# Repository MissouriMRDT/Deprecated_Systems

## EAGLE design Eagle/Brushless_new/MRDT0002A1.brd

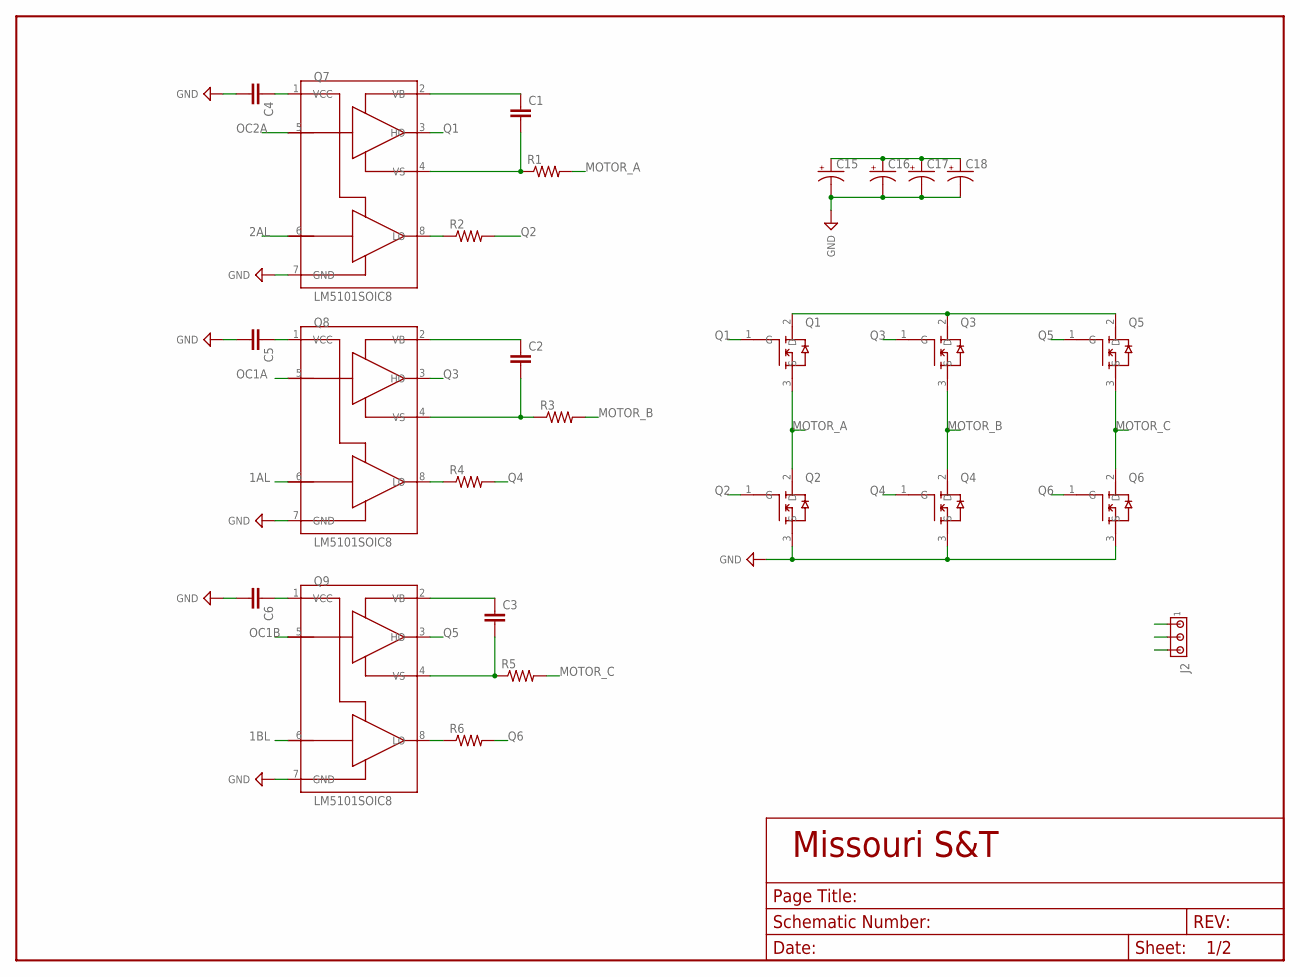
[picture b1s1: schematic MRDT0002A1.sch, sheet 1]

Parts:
C1, C2, C3, C4, C5, C6: C_CAP_1206; C_1206
C15, C16, C17, C18: CAP_POL10MMSM; C_10MMSM
J2: J_MTA3P_156; J_MTA156_3P
Q1, Q2, Q3, Q4, Q5, Q6: N-CH-MOSFETTO252; TO-252
Q7, Q8, Q9: LM5101SOIC8; SOIC8
R1, R2, R3, R4, R5, R6: R_RES_0805; R_0805

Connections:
1AL: Q8.6 (LI); also elsewhere on the board
1BL: Q9.6 (LI); also elsewhere on the board
2AL: Q7.6 (LI); also elsewhere on the board
+12V: C4.1, C5.1, C6.1, Q7.1 (VCC), Q8.1 (VCC), Q9.1 (VCC); also elsewhere on the board
+24V: C15.+, C16.+, C17.+, C18.+, Q1.2 (D), Q3.2 (D), Q5.2 (D)
GND: C4.2, C5.2, C6.2, C15.-, C16.-, C17.-, C18.-, Q2.3 (S), Q4.3 (S), Q6.3 (S), Q7.7 (GND), Q8.7 (GND), Q9.7 (GND); also elsewhere on the board
MOTOR_A: J2.3, Q1.3 (S), Q2.2 (D), R1.2
MOTOR_B: J2.2, Q3.3 (S), Q4.2 (D), R3.2
MOTOR_C: J2.1, Q5.3 (S), Q6.2 (D), R5.2
unnamed: C2.1, Q8.2 (VB)
unnamed: C2.2, Q8.4 (VS), R3.1
unnamed: C3.1, Q9.2 (VB)
unnamed: C3.2, Q9.4 (VS), R5.1
unnamed: C1.1, Q7.2 (VB)
unnamed: C1.2, Q7.4 (VS), R1.1
unnamed: Q8.8 (LO), R4.1
unnamed: Q7.8 (LO), R2.1
unnamed: Q9.8 (LO), R6.1
OC1A: Q8.5 (HI); also elsewhere on the board
OC1B: Q9.5 (HI); also elsewhere on the board
OC2A: Q7.5 (HI); also elsewhere on the board
Q1: Q1.1 (G), Q7.3 (HO)
Q2: Q2.1 (G), R2.2
Q3: Q3.1 (G), Q8.3 (HO)
Q4: Q4.1 (G), R4.2
Q5: Q5.1 (G), Q9.3 (HO)
Q6: Q6.1 (G), R6.2

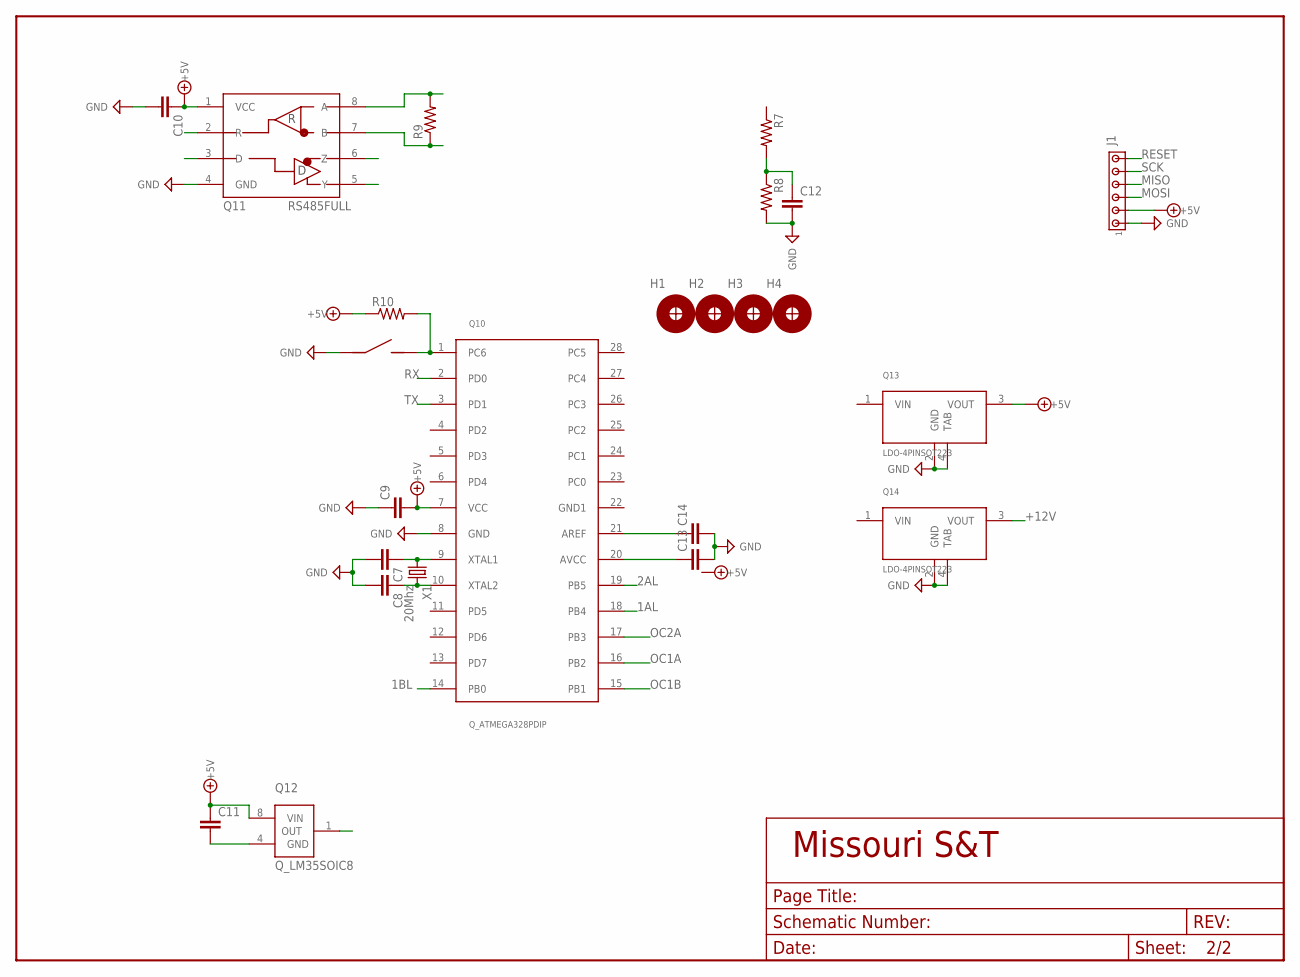
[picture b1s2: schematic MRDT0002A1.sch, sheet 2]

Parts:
C7, C8: C_CAP_1206; C_1206
C9, C10, C11, C12, C13, C14: C_CAP_0805; C_0805
H1, H2, H3, H4: H_MNTHOLE_#4
J1: J_MTA6P_100; J_MTA100_6P
J3: J_MC32857; J_TOGGLE
Q10: Q_ATMEGA328PDIP; DIP28
Q11: RS485FULL; SOIC8
Q12: Q_LM35SOIC8; SOIC8
Q13, Q14: LDO-4PINSOT223; SOT-223
R7, R8, R9, R10: R_RES_0805; R_0805
X1: 20Mhz; HC-49

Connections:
1AL: Q10.18 (PB4); also elsewhere on the board
1BL: Q10.14 (PB0); also elsewhere on the board
2AL: Q10.19 (PB5); also elsewhere on the board
+5V: C9.2, C10.1, C11.1, J1.2, Q10.7 (VCC), Q11.1 (VCC), Q12.8 (VIN), Q13.3 (VOUT), R10.1
+12V: Q14.3 (VOUT); also elsewhere on the board
GND: C7.2, C8.2, C9.1, C10.2, C12.2, C13.2, C14.2, J1.1, J3.P$1 (1), Q10.8 (GND), Q11.4 (GND), Q13.2 (GND), Q13.4 (TAB), Q14.2 (GND), Q14.4 (TAB), R8.2; also elsewhere on the board
MISO: J1.4
MOSI: J1.3
unnamed: J3.P$2 (2), Q10.1 (PC6), R10.2
unnamed: C13.1, Q10.20 (AVCC)
unnamed: C14.1, Q10.21 (AREF)
unnamed: C11.2, Q12.4 (GND)
unnamed: C12.1, R7.2, R8.1
unnamed: Q11.7 (B), R9.1
unnamed: Q11.8 (A), R9.2
unnamed: C7.1, Q10.9 (XTAL1), X1.P$1 (1)
unnamed: C8.1, Q10.10 (XTAL2), X1.P$2 (2)
OC1A: Q10.16 (PB2); also elsewhere on the board
OC1B: Q10.15 (PB1); also elsewhere on the board
OC2A: Q10.17 (PB3); also elsewhere on the board
RESET: J1.6
RX: Q10.2 (PD0), Q11.2 (R)
SCK: J1.5
TX: Q10.3 (PD1), Q11.3 (D)

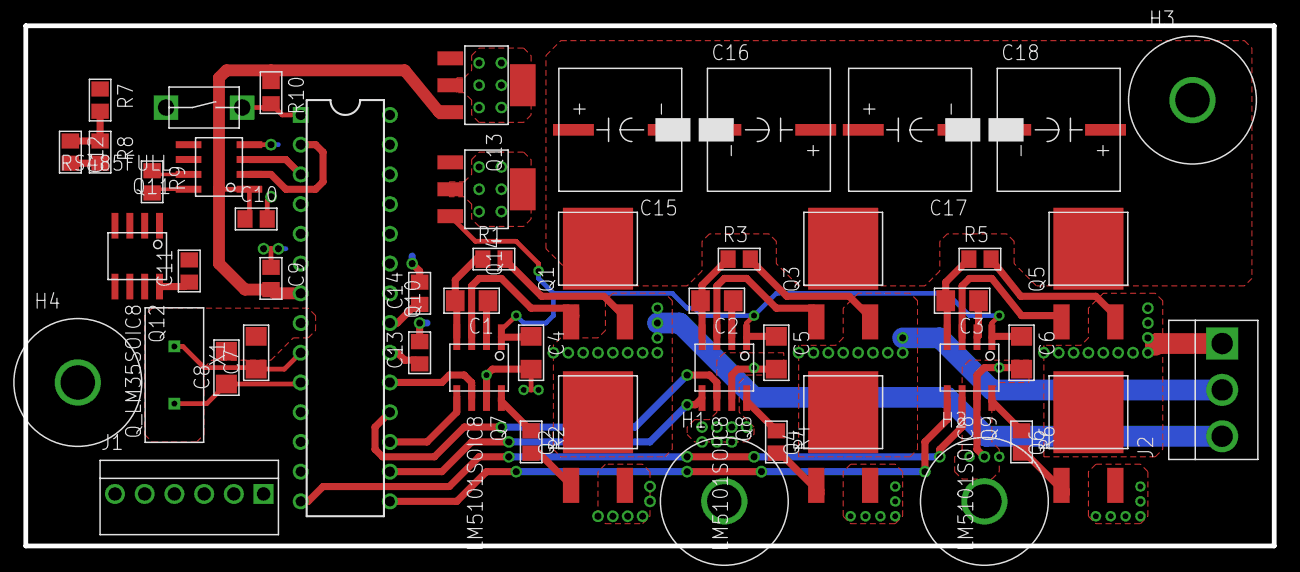
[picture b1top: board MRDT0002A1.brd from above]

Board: 2 copper layers, 106.7 x 44.5 mm, 50 parts (0 on the bottom side), 39 nets.

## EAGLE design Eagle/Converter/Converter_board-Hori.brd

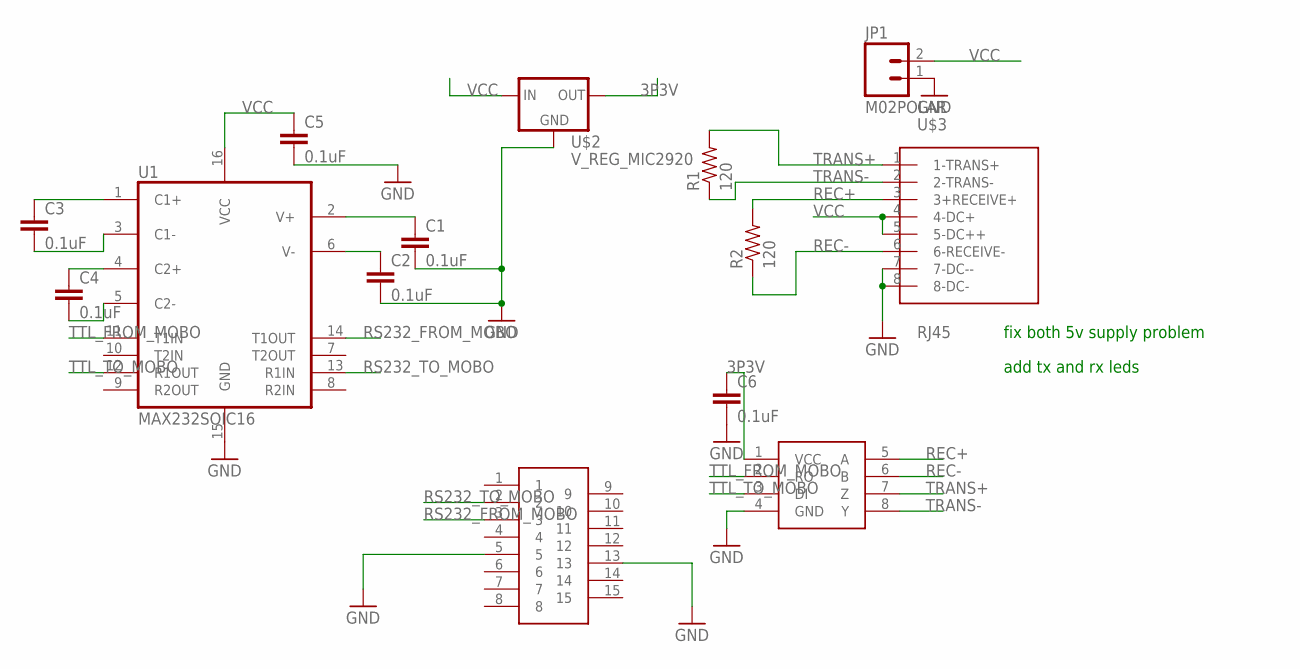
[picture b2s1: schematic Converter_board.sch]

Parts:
C1, C2, C3, C4, C5, C6: 0.1uF; 1206
JP1: M02POLAR; MOLEX-1X2
R1, R2: 120; 1206
U1: MAX232SOIC16; SO016
U$1: MAX3077ESA; SOIC8
U$2: V_REG_MIC2920; SOT223
U$3: RJ45; RJ45-CAT5E
U$4: DB15

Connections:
3P3V: C6.1, U$1.1 (VCC), U$2.3 (OUT)
GND: C1.2, C2.2, C5.2, C6.2, JP1.1, U1.15 (GND), U$1.4 (GND), U$2.2 (GND), U$3.7 (7-DC--), U$3.8 (8-DC-), U$4.5, U$4.13
unnamed: C2.1, U1.6 (V-)
unnamed: C1.1, U1.2 (V+)
unnamed: C3.1, U1.1 (C1+)
unnamed: C3.2, U1.3 (C1-)
unnamed: C4.1, U1.4 (C2+)
unnamed: C4.2, U1.5 (C2-)
REC+: R2.2, U$1.5 (A), U$3.3 (3+RECEIVE+)
REC-: R2.1, U$1.6 (B), U$3.6 (6-RECEIVE-)
RS232_FROM_MOBO: U1.14 (T1OUT), U$4.3
RS232_TO_MOBO: U1.13 (R1IN), U$4.2
TRANS+: R1.2, U$1.7 (Z), U$3.1 (1-TRANS+)
TRANS-: R1.1, U$1.8 (Y), U$3.2 (2-TRANS-)
TTL_FROM_MOBO: U1.11 (T1IN), U$1.2 (RO)
TTL_TO_MOBO: U1.12 (R1OUT), U$1.3 (DI)
VCC: C5.1, JP1.2, U1.16 (VCC), U$2.1 (IN), U$3.4 (4-DC+), U$3.5 (5-DC++)

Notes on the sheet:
fix both 5v supply problem
add tx and rx leds

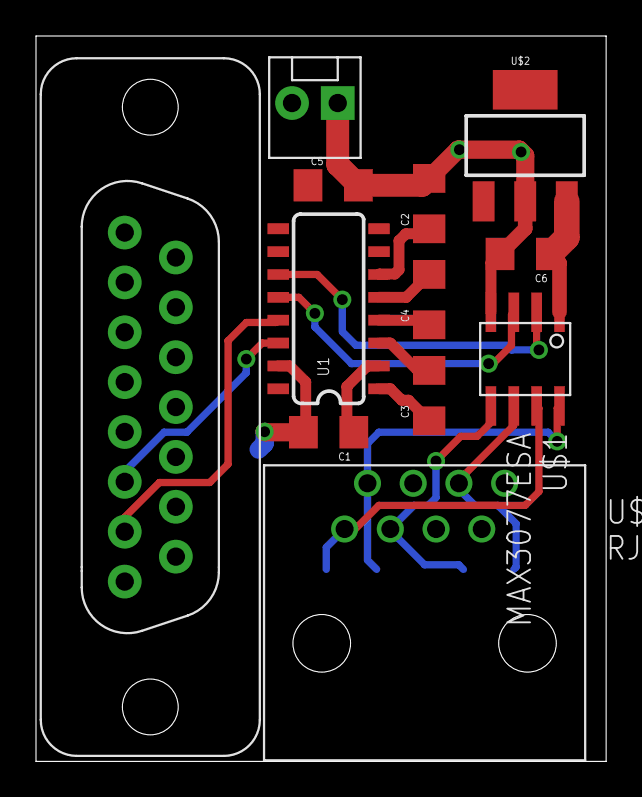
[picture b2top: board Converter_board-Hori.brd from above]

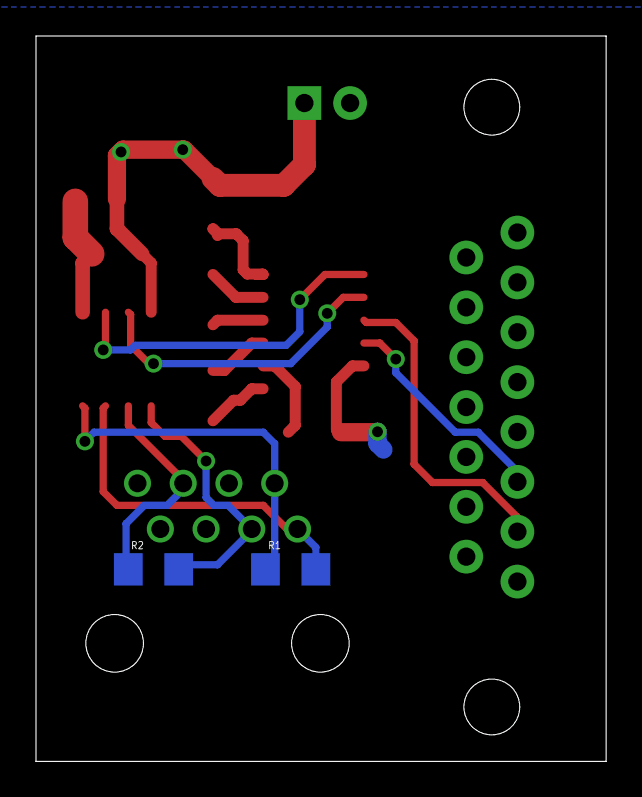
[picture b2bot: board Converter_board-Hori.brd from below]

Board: 2 copper layers, 31.7 x 40.3 mm, 14 parts (2 on the bottom side), 17 nets.

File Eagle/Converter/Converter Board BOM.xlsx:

Partlist exported from C:/Users/Mike M/Documents/GitHub/Motor-Controller/Eagle/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
Qty | Value | Device | Package | Parts | Description | NEWARK
6 | 0.1uF | CAP1206 | 1206 | C1, C2, C3, C4, C5, C6 | Capacitor | 70K9281
2 | 120 | RESISTOR1206 | 1206 | R1, R2 | Resistor | 64R5435
1 | DB15 | DB15 | DB15 | U$4 |  | 15J5329
1 | MAX3077ESA | MAX3077ESA | SOIC8 | U$1 |  | MAX3077ESA
1 | MAX3232 | MAX3232 | SOIC16 | U$2
1 | RJ45 | RJ45 | RJ45-CAT5E | U$3

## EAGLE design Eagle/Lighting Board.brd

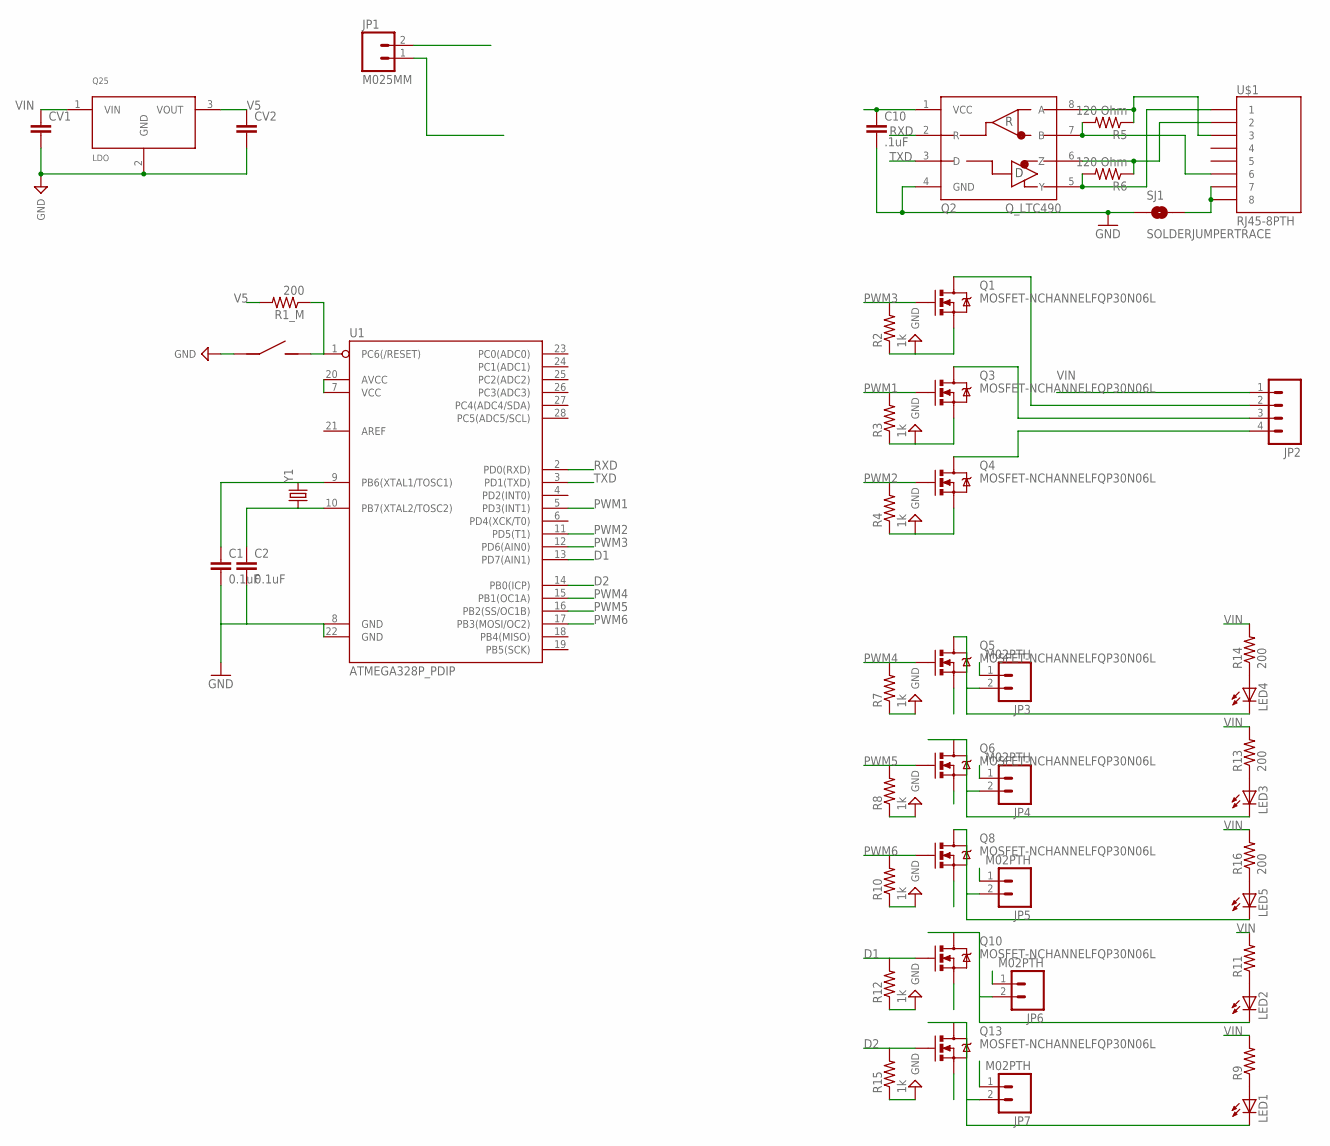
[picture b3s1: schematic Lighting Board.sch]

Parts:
C1, C2: 0.1uF; 1206
C10: .1uF; 1206
CV1, CV2: C_CAP_0805; C_0805
JP1: M025MM; SCREWTERMINAL-5MM-2
JP2: M04PTH; 1X04
JP3, JP4, JP5, JP6, JP7: M02PTH; 1X02
LED1, LED2, LED3, LED4, LED5: LED1206; LED-1206
MS: J_MC32857; J_TOGGLE
Q1, Q3, Q4, Q5, Q6, Q8, Q10, Q13: MOSFET-NCHANNELFQP30N06L; TO220V
Q2: Q_LTC490; DIP8
Q25: LDO; TO-220
R1_M: 200; R_0805
R2, R3, R4, R7, R8, R10, R12, R15: 1k; 1206
R5, R6: 120 Ohm; 1206
R9, R11: RESISTOR1206; 1206
R13, R14, R16: 200; 1206
SJ1: SOLDERJUMPERTRACE; SJ_2S-TRACE
U1: ATMEGA328P_PDIP; DIL28-3
U$1: RJ45-8PTH; RJ45-8
Y1: CRYSTALHC49US; HC49US

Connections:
D1: Q10.1 (G), R12.2, U1.13 (PD7(AIN1))
D2: Q13.1 (G), R15.2, U1.14 (PB0(ICP))
GND: C1.2, C2.2, C10.2, CV1.2, CV2.2, JP1.2, MS.P$1 (1), Q1.3 (S), Q2.4 (GND), Q3.3 (S), Q4.3 (S), Q5.3 (S), Q6.3 (S), Q8.3 (S), Q10.3 (S), Q13.3 (S), Q25.2 (GND), R2.1, R3.1, R4.1, R7.1, R8.1, R10.1, R12.1, R15.1, SJ1.1, U1.8 (GND), U1.22 (GND)
unnamed: Q2.5 (Y), R6.2, U$1.1
unnamed: C2.1, U1.10 (PB7(XTAL2/TOSC2)), Y1.1
unnamed: LED1.A, R9.1
unnamed: LED2.A, R11.1
unnamed: LED3.A, R13.1
unnamed: LED4.A, R14.1
unnamed: LED5.A, R16.1
unnamed: Q2.6 (Z), R6.1, U$1.2
unnamed: Q2.7 (B), R5.2, U$1.6
unnamed: Q2.8 (A), R5.1, U$1.3
unnamed: SJ1.2, U$1.7, U$1.8
unnamed: C1.1, U1.9 (PB6(XTAL1/TOSC1)), Y1.2
unnamed: JP2.2, Q1.2 (D)
unnamed: JP2.3, Q3.2 (D)
unnamed: JP2.4, Q4.2 (D)
unnamed: MS.P$2 (2), R1_M.1, U1.1 (PC6(/RESET))
N%2: JP4.2, LED3.C, Q6.2 (D)
N%3: JP3.2, LED4.C, Q5.2 (D)
N%106: JP5.2, LED5.C, Q8.2 (D)
N%107: JP6.2, LED2.C, Q10.2 (D)
N%110: JP7.2, LED1.C, Q13.2 (D)
PWM1: Q3.1 (G), R3.2, U1.5 (PD3(INT1))
PWM2: Q4.1 (G), R4.2, U1.11 (PD5(T1))
PWM3: Q1.1 (G), R2.2, U1.12 (PD6(AIN0))
PWM4: Q5.1 (G), R7.2, U1.15 (PB1(OC1A))
PWM5: Q6.1 (G), R8.2, U1.16 (PB2(SS/OC1B))
PWM6: Q8.1 (G), R10.2, U1.17 (PB3(MOSI/OC2))
RXD: Q2.2 (R), U1.2 (PD0(RXD))
TXD: Q2.3 (D), U1.3 (PD1(TXD))
V5: C10.1, CV2.1, Q2.1 (VCC), Q25.3 (VOUT), R1_M.2, U1.7 (VCC), U1.20 (AVCC)
VIN: CV1.1, JP1.1, JP2.1, JP3.1, JP4.1, JP5.1, JP6.1, JP7.1, Q25.1 (VIN), R9.2, R11.2, R13.2, R14.2, R16.2

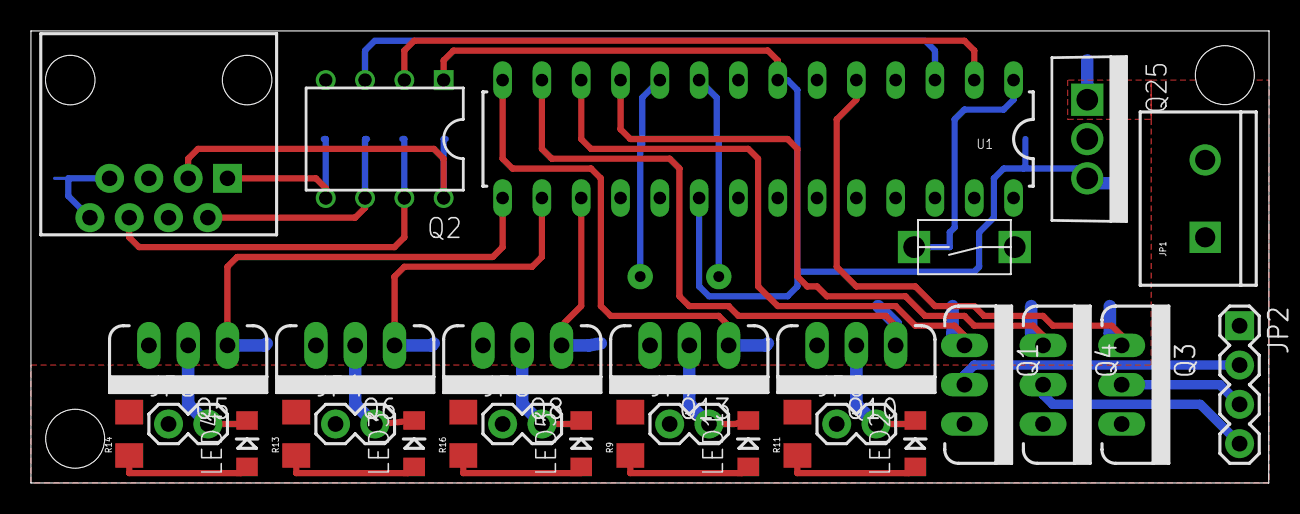
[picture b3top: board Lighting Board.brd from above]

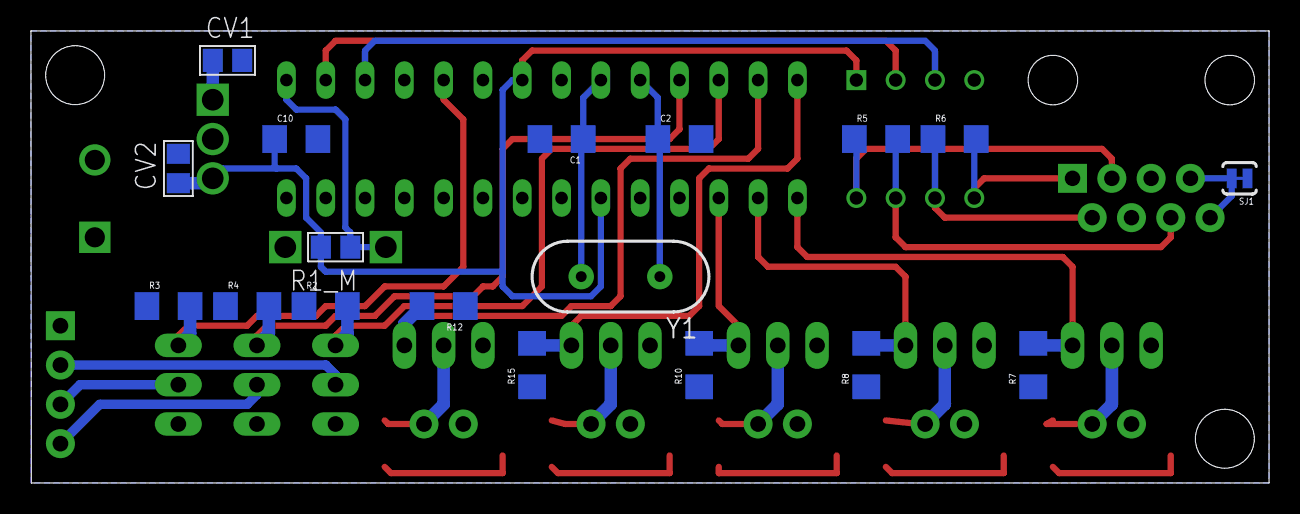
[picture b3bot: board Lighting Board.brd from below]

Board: 2 copper layers, 80.0 x 29.2 mm, 48 parts (18 on the bottom side), 34 nets.

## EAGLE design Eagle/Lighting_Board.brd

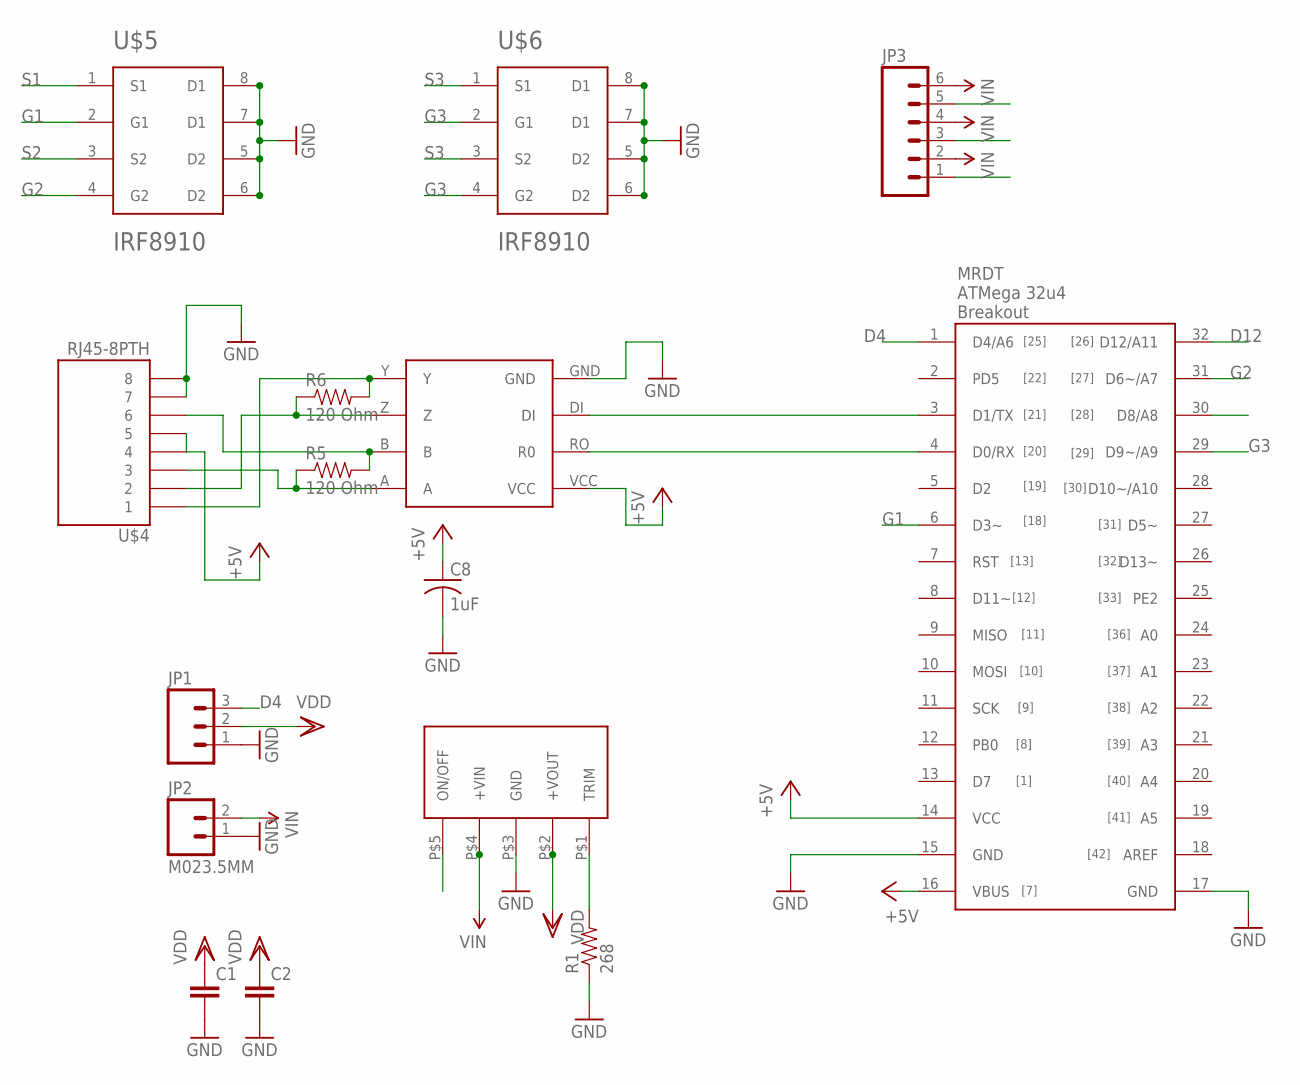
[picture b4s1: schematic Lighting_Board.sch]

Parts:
C1, C2: CAP1206; 1206
C8: 1uF; C1206
JP1: M03SCREW; SCREWTERMINAL-3.5MM-3
JP2: M023.5MM; SCREWTERMINAL-3.5MM-2
JP3: M063.5MM-6; SCREWTERMINAL-3.5MM-6
R1: 268; 1206
R5, R6: 120 Ohm; 1206
U$1: OKR-T/10-W12-C
U$2: 32U4_BREAKOUT; 32U4_MCU_DIP
U$3: MAX3077; MAX3070E
U$4: RJ45-8PTH; RJ45-8
U$5, U$6: IRF8910; SO8

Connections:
+5V: C8.1, U$2.14 (VCC), U$2.16 (VBUS), U$3.VCC, U$4.4, U$4.5
D4: JP1.3, U$2.1 (D4/A6)
D8: U$1.P$5 (ON/OFF), U$2.30 (D8/A8)
D12: U$2.32 (D12/A11)
G1: U$2.6 (D3~), U$5.2 (G1)
G2: U$2.31 (D6~/A7), U$5.4 (G2)
G3: U$2.29 (D9~/A9), U$6.2 (G1), U$6.4 (G2)
GND: C1.2, C2.2, C8.2, JP1.1, JP2.1, R1.1, U$1.P$3 (GND), U$2.15 (GND), U$2.17 (GND), U$3.GND, U$4.7, U$4.8, U$5.5 (D2), U$5.6 (D2), U$5.7 (D1), U$5.8 (D1), U$6.5 (D2), U$6.6 (D2), U$6.7 (D1), U$6.8 (D1)
unnamed: R1.2, U$1.P$1 (TRIM)
unnamed: R6.2, U$3.Y, U$4.1
unnamed: R6.1, U$3.Z, U$4.2
unnamed: R5.2, U$3.B, U$4.6
unnamed: R5.1, U$3.A, U$4.3
unnamed: U$2.3 (D1/TX), U$3.DI
RXD: U$2.4 (D0/RX), U$3.RO (R0)
S1: JP3.5, U$5.1 (S1)
S2: JP3.3, U$5.3 (S2)
S3: JP3.1, U$6.1 (S1), U$6.3 (S2)
VDD: C1.1, C2.1, JP1.2, U$1.P$2 (+VOUT)
VIN: JP2.2, JP3.2, JP3.4, JP3.6, U$1.P$4 (+VIN)

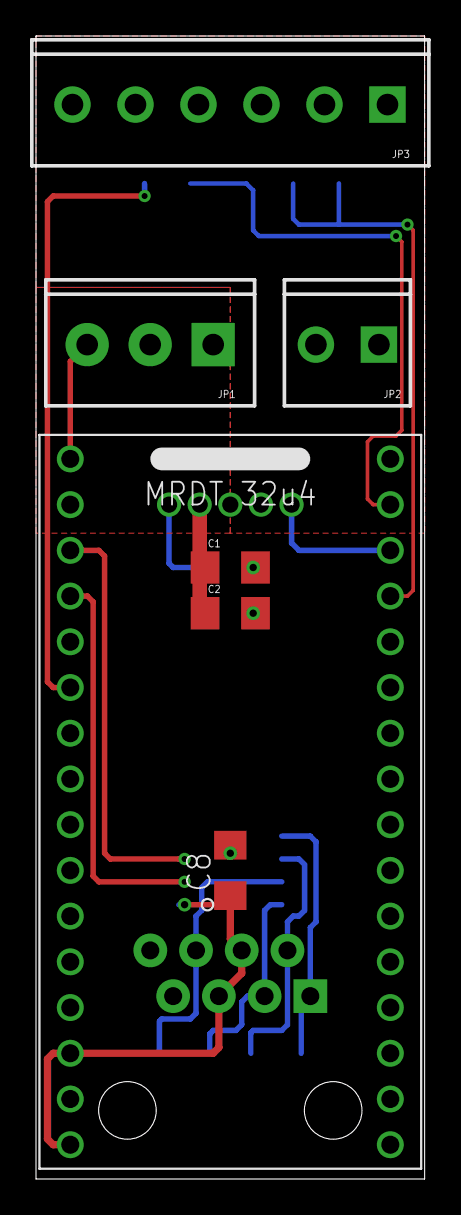
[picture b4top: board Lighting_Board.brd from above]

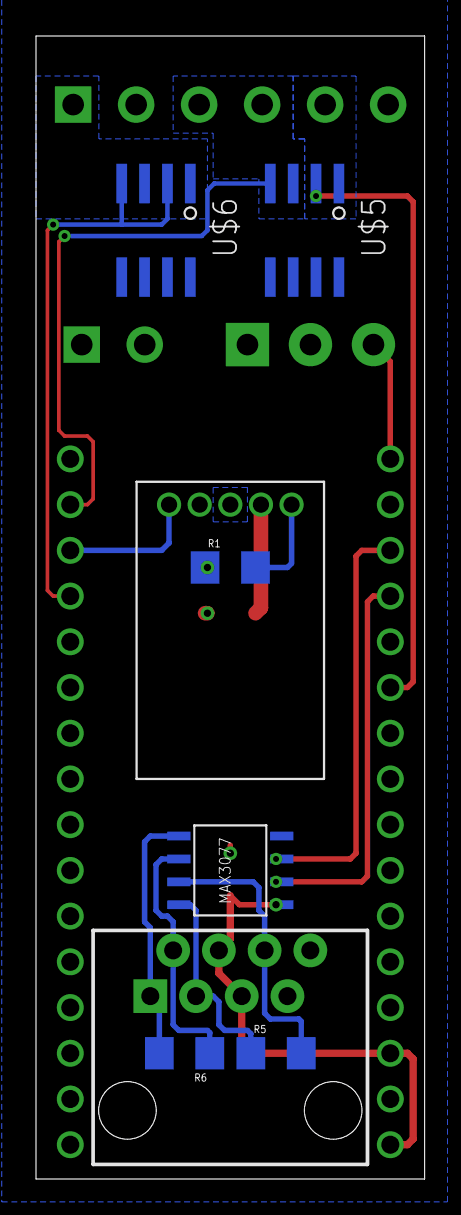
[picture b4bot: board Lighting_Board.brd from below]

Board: 2 copper layers, 21.6 x 63.5 mm, 15 parts (8 on the bottom side), 19 nets.

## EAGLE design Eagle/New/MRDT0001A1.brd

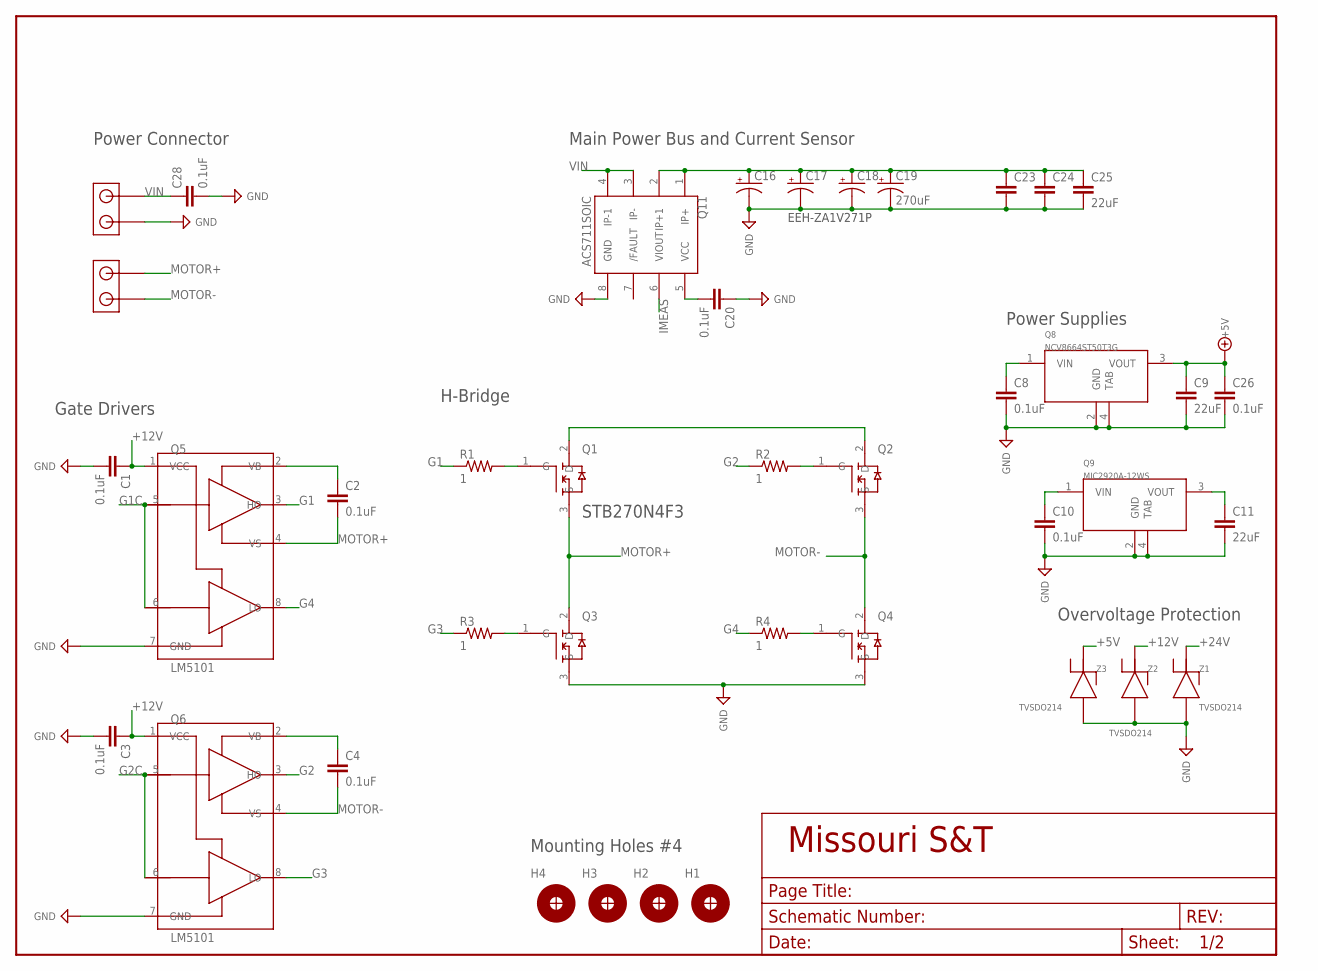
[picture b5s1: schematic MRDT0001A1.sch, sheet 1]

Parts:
C1, C3, C28: 0.1uF; C_0805
C2, C4, C8, C10, C20, C26: 0.1uF; C_1206
C9, C11, C25: 22uF; C_1206
C16, C17, C18: CAP_POL10MMSM; C_10MMSM
C19: 270uF; C_10MMSM
C23, C24: C_CAP_1206; C_1206
H1, H2, H3, H4: H_MNTHOLE_#4
J4, J5: J_1546074-2; THERM_BLOCK_2
Q1, Q2, Q3, Q4: N-CH-MOSFETTO263; TO-263
Q5, Q6: LM5101; SOIC8
Q8: NCV8664ST50T3G; SOT-223
Q9: MIC2920A-12WS; SOT-223
Q11: ACS711SOIC; SOIC8
R1, R2, R3, R4: 1; R_0805
Z1, Z2, Z3: TVSDO214; DO-214AC

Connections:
+5V: C9.1, C26.1, Q8.3 (VOUT), Z3.C; also elsewhere on the board
+12V: C1.1, C3.1, C11.1, Q5.1 (VCC), Q6.1 (VCC), Q9.3 (VOUT), Z2.C
+24V: C10.1, C16.+, C17.+, C18.+, C19.+, C23.1, C24.1, C25.1, Q1.2 (D), Q2.2 (D), Q9.1 (VIN), Q11.1 (IP+), Q11.2 (IP+1), Z1.C; also elsewhere on the board
G1: Q5.3 (HO), R1.1
G1C: Q5.5 (HI), Q5.6 (LI); also elsewhere on the board
G2: Q6.3 (HO), R2.1
G2C: Q6.5 (HI), Q6.6 (LI); also elsewhere on the board
G3: Q6.8 (LO), R3.1
G4: Q5.8 (LO), R4.1
GND: C1.2, C3.2, C8.2, C9.2, C10.2, C11.2, C16.-, C17.-, C18.-, C19.-, C20.1, C23.2, C24.2, C25.2, C26.2, C28.2, J4.P$1, Q3.3 (S), Q4.3 (S), Q5.7 (GND), Q6.7 (GND), Q8.2 (GND), Q8.4 (TAB), Q9.2 (GND), Q9.4 (TAB), Q11.8 (GND), Z1.A, Z2.A, Z3.A; also elsewhere on the board
IMEAS: Q11.6 (VIOUT); also elsewhere on the board
MOTOR+: C2.2, J5.P$2, Q1.3 (S), Q3.2 (D), Q5.4 (VS)
MOTOR-: C4.2, J5.P$1, Q2.3 (S), Q4.2 (D), Q6.4 (VS)
unnamed: Q1.1 (G), R1.2
unnamed: Q3.1 (G), R3.2
unnamed: Q2.1 (G), R2.2
unnamed: Q4.1 (G), R4.2
unnamed: C2.1, Q5.2 (VB)
unnamed: C4.1, Q6.2 (VB)
unnamed: C20.2, Q11.5 (VCC)
VIN: C8.1, C28.1, J4.P$2, Q8.1 (VIN), Q11.3 (IP-), Q11.4 (IP-1)

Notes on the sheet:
EEH-ZA1V271P
Power Connector
Gate Drivers
H-Bridge
Overvoltage Protection
Mounting Holes #4
Power Supplies
Main Power Bus and Current Sensor
STB270N4F3

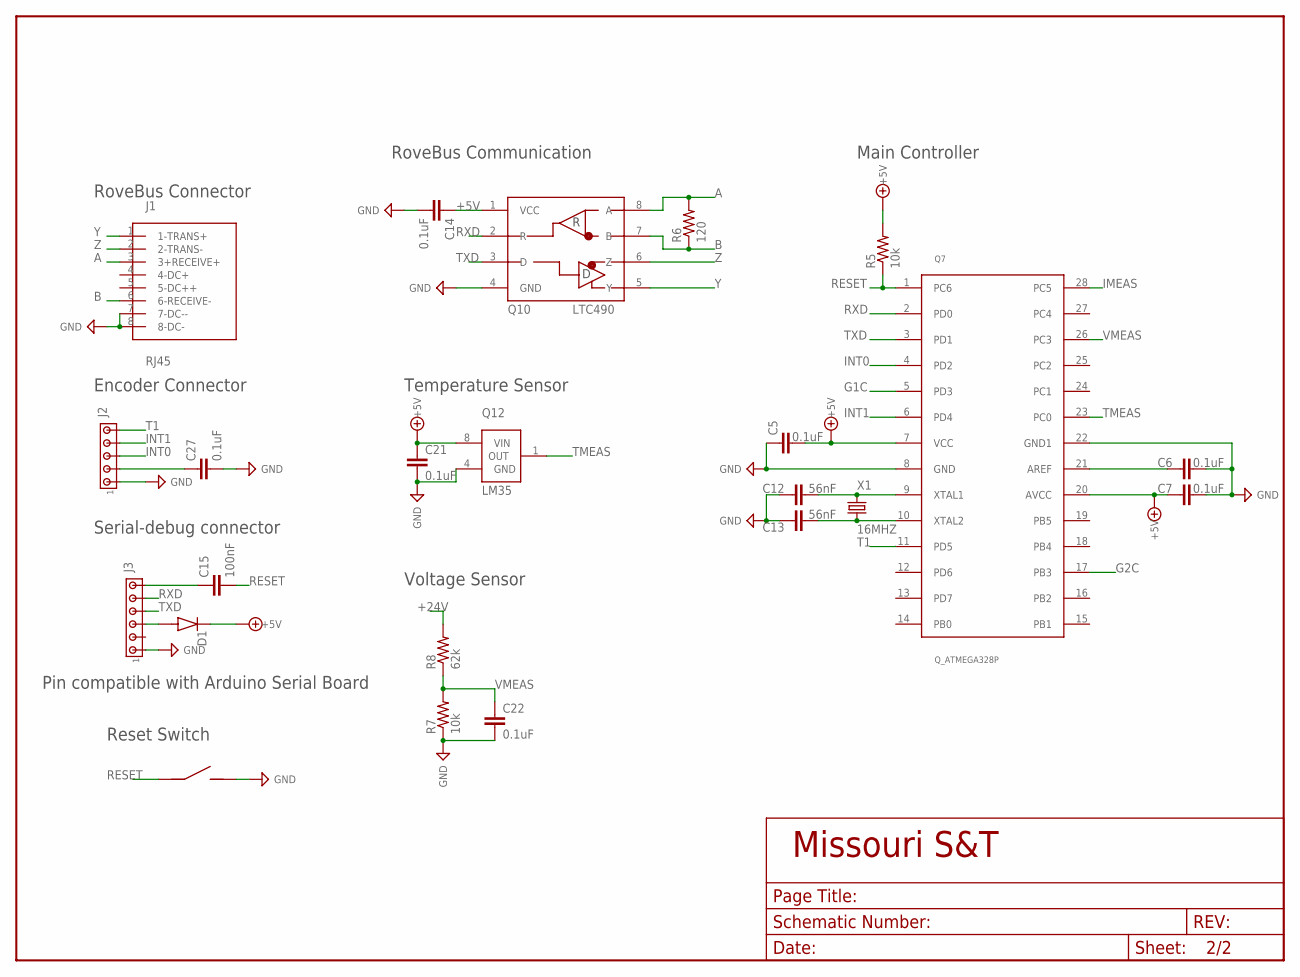
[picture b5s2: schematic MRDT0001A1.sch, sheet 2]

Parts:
C5, C6, C7, C14, C21, C22, C27: 0.1uF; C_0805
C12, C13: 56nF; C_1206
C15: 100nF; C_0805
D1: D_DIODEDO214AC; DO-214AC
J1: RJ45; RJ45-CAT5E
J2: J_MTA5P_100; J_MTA100_5P
J3: J_MTA6P_100; J_MTA100_6P
J6: J_MC32857; J_TOGGLE
Q7: Q_ATMEGA328P; DIP28
Q10: LTC490; SOIC8
Q12: LM35; SOIC8
R5, R7: 10k; R_0805
R6: 120; R_0805
R8: 62k; R_0805
X1: 16MHZ; HC-49

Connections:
+5V: C5.2, C7.1, C14.1, C21.1, C27.1, D1.C, J2.2, Q7.7 (VCC), Q7.20 (AVCC), Q10.1 (VCC), Q12.8 (VIN), R5.2; also elsewhere on the board
+24V: R8.2; also elsewhere on the board
A: J1.3 (3+RECEIVE+), Q10.8 (A), R6.2
B: J1.6 (6-RECEIVE-), Q10.7 (B), R6.1
EXTRESET: C15.1, J3.6
G1C: Q7.5 (PD3); also elsewhere on the board
G2C: Q7.17 (PB3); also elsewhere on the board
GND: C5.1, C6.2, C7.2, C12.1, C13.1, C14.2, C21.2, C22.2, C27.2, J1.7 (7-DC--), J1.8 (8-DC-), J2.1, J3.1, J6.P$2 (2), Q7.8 (GND), Q7.22 (GND1), Q10.4 (GND), Q12.4 (GND), R7.1; also elsewhere on the board
IMEAS: Q7.28 (PC5); also elsewhere on the board
INT0: J2.3, Q7.4 (PD2)
INT1: J2.4, Q7.6 (PD4)
unnamed: C12.2, Q7.9 (XTAL1), X1.P$1 (1)
unnamed: C6.1, Q7.21 (AREF)
unnamed: D1.A, J3.3
unnamed: C13.2, Q7.10 (XTAL2), X1.P$2 (2)
RESET: C15.2, J6.P$1 (1), Q7.1 (PC6), R5.1
RXD: J3.5, Q7.2 (PD0), Q10.2 (R)
T1: J2.5, Q7.11 (PD5)
TMEAS: Q7.23 (PC0), Q12.1 (OUT)
TXD: J3.4, Q7.3 (PD1), Q10.3 (D)
VMEAS: C22.1, Q7.26 (PC3), R7.2, R8.1
Y: J1.1 (1-TRANS+), Q10.5 (Y)
Z: J1.2 (2-TRANS-), Q10.6 (Z)

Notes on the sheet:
RoveBus Connector
Encoder Connector
Serial-debug connector
Pin compatible with Arduino Serial Board
Reset Switch
RoveBus Communication
Temperature Sensor
Voltage Sensor
Main Controller

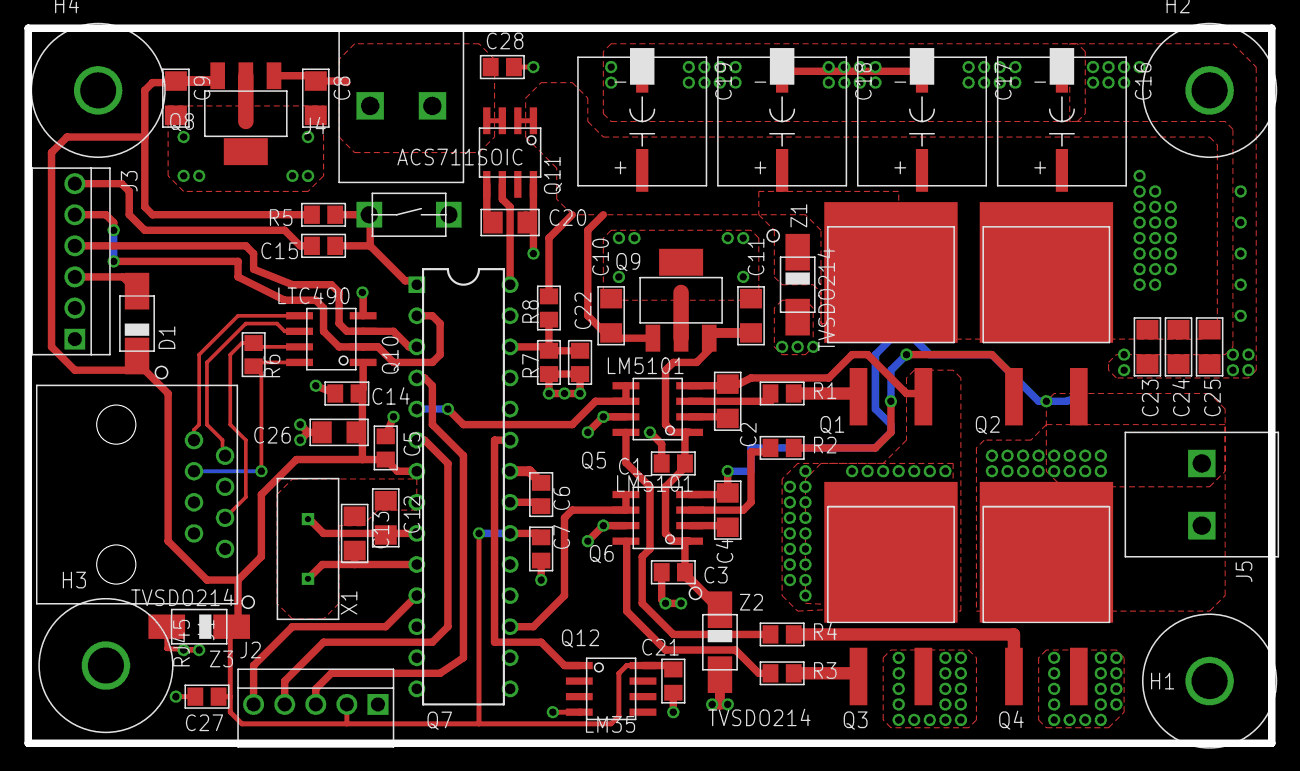
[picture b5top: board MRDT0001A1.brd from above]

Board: 2 copper layers, 101.6 x 58.4 mm, 63 parts (0 on the bottom side), 38 nets.

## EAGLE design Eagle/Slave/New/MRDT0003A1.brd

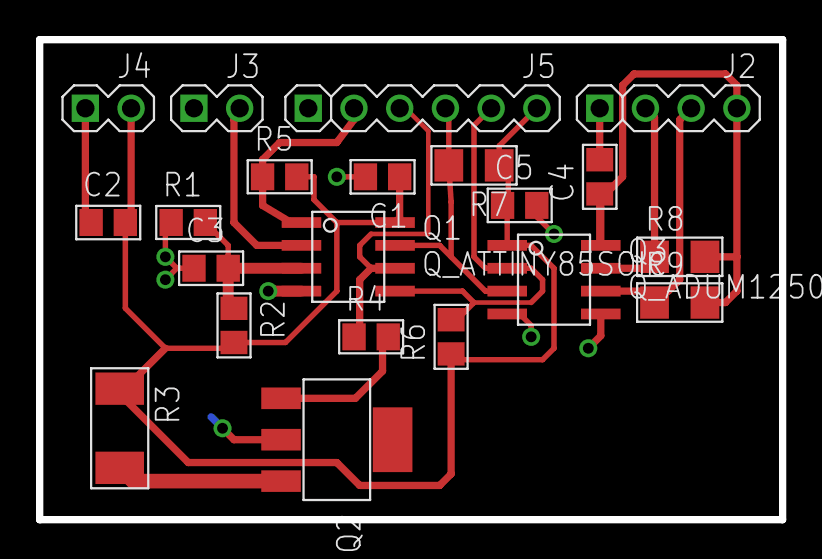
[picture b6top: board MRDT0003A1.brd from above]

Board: 2 copper layers, 41.3 x 26.7 mm, 21 parts (0 on the bottom side), 14 nets.

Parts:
C1, C4, C5: 0.1uF; C_0805
C2: 1uF; C_0805
C3: 0.01uF; C_0805
J2: J_BRK1X4_100MIL
J3, J4: J_HDR1X2_BRK_100MIL; J_BRK1X2_100MIL
J5: J_BRK1X6_100MIL
Q1: Q_ATTINY85SOIC; SOIC8
Q2: Q_BSP315P; SOT-223
Q3: Q_ADUM1250SOIC; SOIC8
R1: 100k; R_0805
R2: 71.87k; R_0805
R3: 20; R_2010
R4: 210; R_0805
R5, R6: R_0805
R7, R8, R9: R_1206

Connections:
BATTERY: C1.1, C2.2, C5.1, J4.2, J5.6, Q1.8, Q3.1, R2.2, R3.1, R5.2, R6.1, R7.1
GATE: J5.3, Q1.6, R4.1
GND: C1.2, C2.1, C3.1, C5.2, J3.1, J4.1, J5.1, Q1.4, Q2.2, Q3.4, R1.1
GND1: C4.2, J2.1, Q3.5
unnamed: Q2.1, R4.2
unnamed: Q2.3, R3.2
RESET: J5.2, Q1.1, R5.1
SCL1: J5.4, Q1.7, Q3.3, R7.2
SCL2: J2.3, Q3.6, R9.1
SDA1: J5.5, Q1.5, Q3.2, R6.2
SDA2: J2.2, Q3.7, R8.1
TEMP: J3.2, Q1.2
VCC1: C4.1, J2.4, Q3.8, R8.2, R9.2
VOLTAGE: C3.2, Q1.3, R1.2, R2.1

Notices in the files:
parts and their libraries:
SparkFun-Capacitors: Licensing: Creative Commons ShareAlike 4.0 International - https://creativecommons.org/licenses/by-sa/4.0
SparkFun-DigitalIC: Licensing: CC v3.0 Share-Alike You are welcome to use this library for commercial purposes.
